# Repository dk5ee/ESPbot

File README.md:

# ESPbot
Another ESP32-cam based robot project

The repository contains:

* espcam - kicad footprint and library for ESP32-CAM
* TP5400 - kicad footprint and library for TP5400 and ESOP-8
* espbot - kicad project for a motherboard, clone of https://github.com/c3d2/C3-PR/tree/master/pcb

## Considerations TBD

* 0402 or 0805 or other footprints for resistors - make the pcb easier or make it smaller
* same for capacitors
* also capacitors: MLCC or electrolytics for the microfarad caps
* document the reset logic - does this work as intended?
* footprint for the inductor
* which usb socket?
* maximum pcb dimensions - more squarish or more longish?
* also pcb: where should the camera be located on the the assembly - more in the middle or on a side?
* also pcb: where should the antenna be located? on top, protruding over the edge of the motherboard?
* heat problem: the tp5400 and the esp32 will generate heat
* maybe power the motordriver directly from battery power, if the motor allows that
* consider alternatives to TP4500
* the inverters to save pins eliminate the possibility to do a motor brake

## Differences to C3-PR design

* made with kicad instead of easyeda
* instead of power from a USB powerbank this design uses a TP4500 power management chip
* instead of the dual NPN transistor every transistor is the same mosfet

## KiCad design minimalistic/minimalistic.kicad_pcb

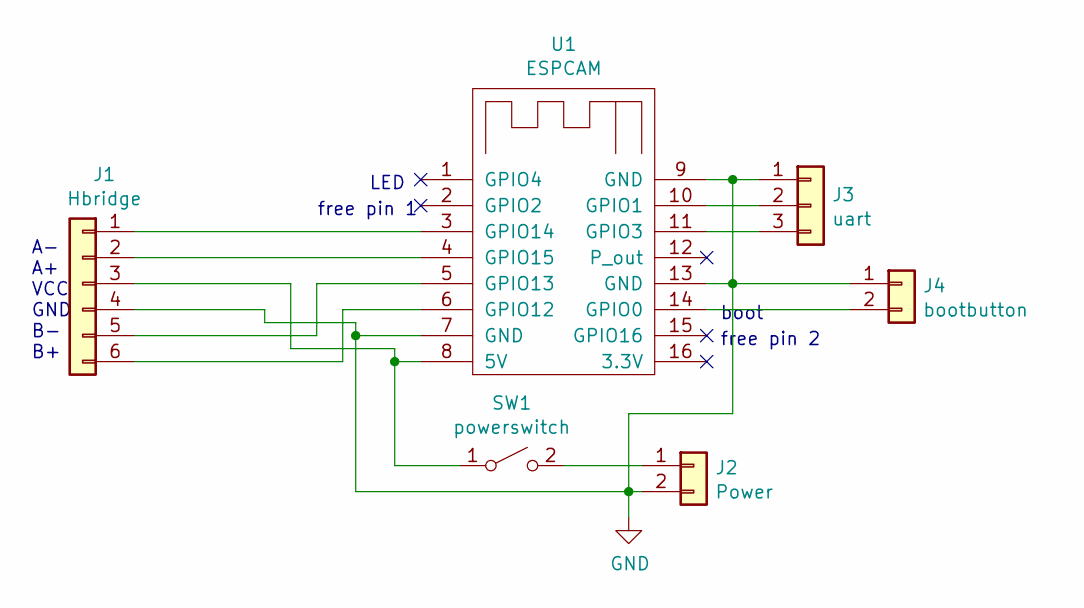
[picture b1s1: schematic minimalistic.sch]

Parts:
J1: Hbridge; PinHeader_1x06_P2.54mm_Vertical
J2: Power; JST_EH_B2B-EH-A_1x02_P2.50mm_Vertical
J3: uart; PinHeader_1x03_P2.54mm_Vertical
J4: bootbutton; PinHeader_1x02_P2.54mm_Vertical
SW1: powerswitch; PinHeader_1x02_P2.54mm_Vertical
U1: ESPCAM; ESPCAM_bottom

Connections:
GND: J1.4, J2.2, J3.1, J4.1, U1.7 (GND), U1.9 (GND), U1.13 (GND)
unnamed: J1.1, U1.3 (GPIO14)
unnamed: J1.2, U1.4 (GPIO15)
unnamed: J1.3, SW1.1 (A), U1.8 (5V)
unnamed: J1.5, U1.5 (GPIO13)
unnamed: J1.6, U1.6 (GPIO12)
unnamed: J2.1, SW1.2 (B)
unnamed: J3.2, U1.10 (GPIO1)
unnamed: J3.3, U1.11 (GPIO3)
unnamed: J4.2, U1.14 (GPIO0)

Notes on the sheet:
A- A+ VCC GND B- B+
LED
boot
free pin 1
free pin 2

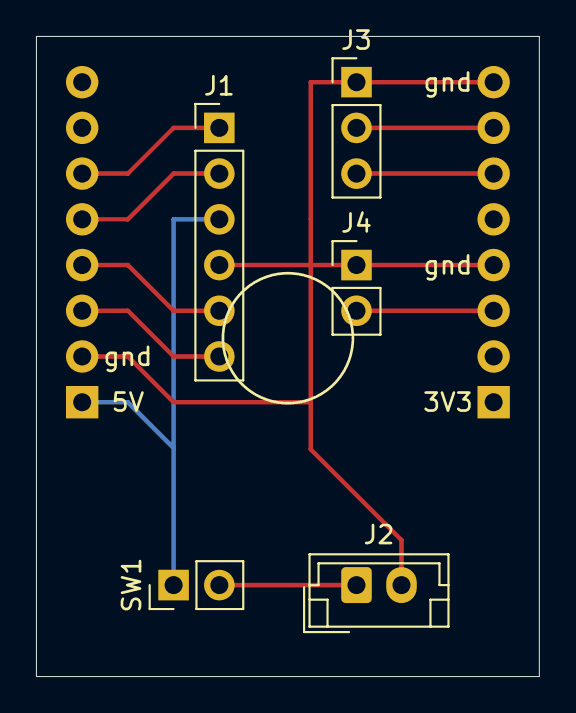
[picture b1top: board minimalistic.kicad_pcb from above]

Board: 2 copper layers, 27.9 x 35.6 mm, 6 parts (0 on the bottom side), 10 nets.

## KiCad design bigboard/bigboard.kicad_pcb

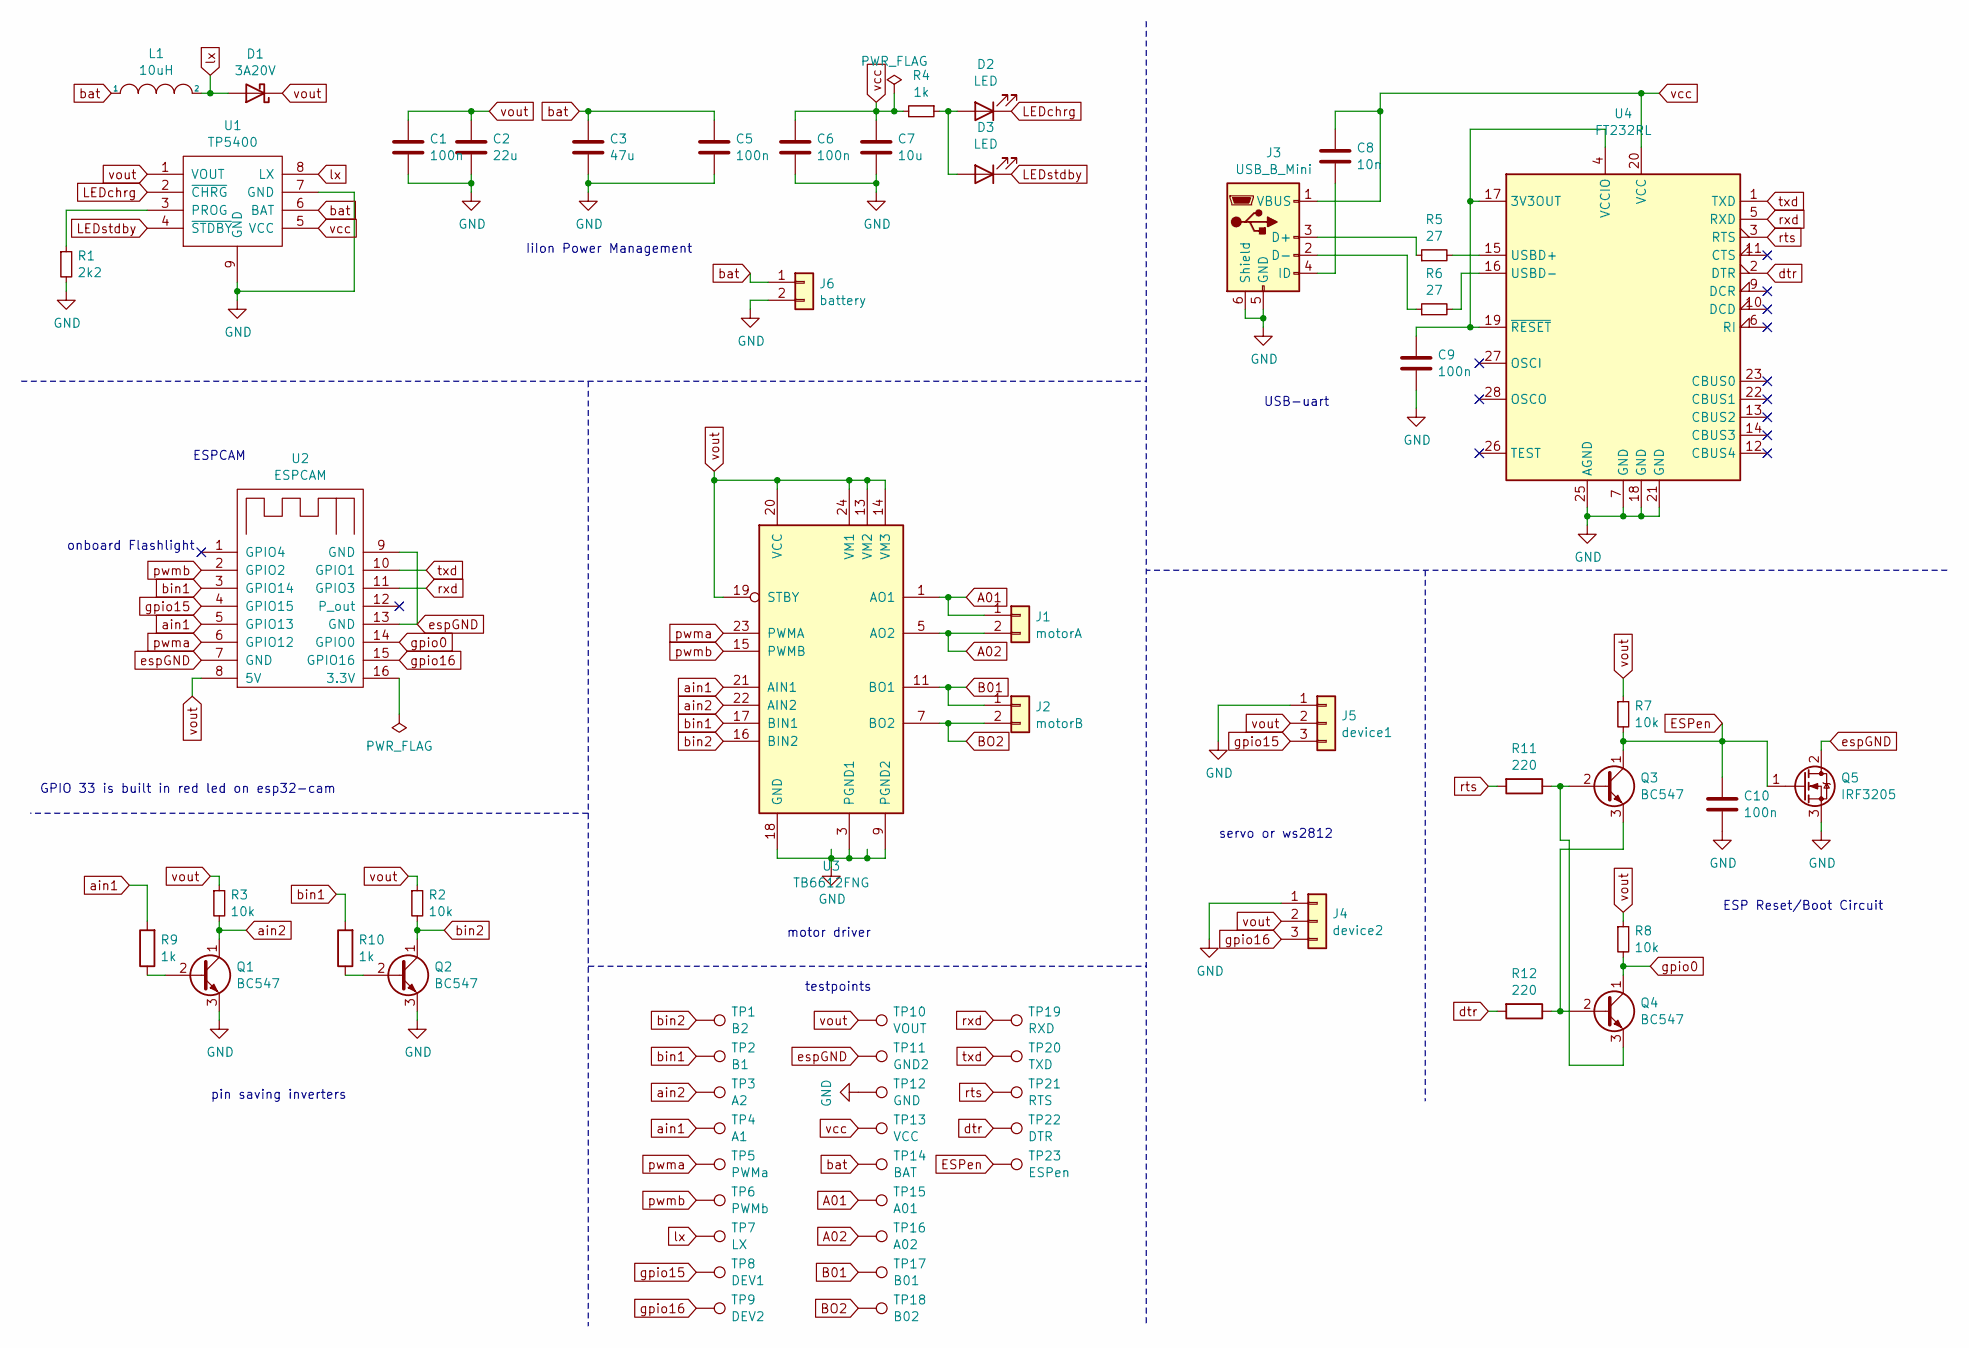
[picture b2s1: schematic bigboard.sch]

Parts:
C1, C5, C6, C9, C10: 100n; C_Disc_D3.0mm_W1.6mm_P2.50mm
C2: 22u; CP_Radial_D10.0mm_P2.50mm_P5.00mm
C3: 47u; CP_Radial_D10.0mm_P2.50mm_P5.00mm
C7: 10u; CP_Radial_D10.0mm_P2.50mm_P5.00mm
C8: 10n; C_Disc_D4.3mm_W1.9mm_P5.00mm
D1: 3A20V; D_A-405_P7.62mm_Horizontal
D2, D3: LED; LED_D3.0mm
J1: motorA; PinHeader_1x02_P2.54mm_Vertical
J2: motorB; PinHeader_1x02_P2.54mm_Vertical
J3: USB_B_Mini; USB_Micro-B_Amphenol_10118194_Horizontal
J4: device2; PinHeader_1x03_P2.54mm_Vertical
J5: device1; PinHeader_1x03_P2.54mm_Vertical
J6: battery; PinHeader_1x02_P2.54mm_Vertical
L1: 10uH; L_Toroid_Vertical_L10.0mm_W5.0mm_P5.08mm
Q1, Q2, Q3, Q4: BC547; TO-92_Inline
Q5: IRF3205; TO-220F-3_Horizontal_TabDown
R1: 2k2; R_Axial_DIN0204_L3.6mm_D1.6mm_P5.08mm_Horizontal
R2, R3, R7, R8: 10k; R_Axial_DIN0204_L3.6mm_D1.6mm_P5.08mm_Horizontal
R4, R9, R10: 1k; R_Axial_DIN0204_L3.6mm_D1.6mm_P5.08mm_Horizontal
R5, R6: 27; R_Axial_DIN0204_L3.6mm_D1.6mm_P5.08mm_Horizontal
R11, R12: 220; R_Axial_DIN0204_L3.6mm_D1.6mm_P5.08mm_Horizontal
TP1: B2; TestPoint_Bridge_Pitch2.54mm_Drill0.7mm
TP2: B1; TestPoint_Bridge_Pitch2.54mm_Drill0.7mm
TP3: A2; TestPoint_Bridge_Pitch2.54mm_Drill0.7mm
TP4: A1; TestPoint_Bridge_Pitch2.54mm_Drill0.7mm
TP5: PWMa; TestPoint_Bridge_Pitch2.54mm_Drill0.7mm
TP6: PWMb; TestPoint_Bridge_Pitch2.54mm_Drill0.7mm
TP7: LX; TestPoint_Bridge_Pitch2.54mm_Drill0.7mm
TP8: DEV1; TestPoint_Bridge_Pitch2.54mm_Drill0.7mm
TP9: DEV2; TestPoint_Bridge_Pitch2.54mm_Drill0.7mm
TP10: VOUT; TestPoint_Bridge_Pitch2.54mm_Drill0.7mm
TP11: GND2; TestPoint_Bridge_Pitch2.54mm_Drill0.7mm
TP12: GND; TestPoint_Bridge_Pitch2.54mm_Drill0.7mm
TP13: VCC; TestPoint_Bridge_Pitch2.54mm_Drill0.7mm
TP14: BAT; TestPoint_Bridge_Pitch2.54mm_Drill0.7mm
TP15: A01; TestPoint_Bridge_Pitch2.54mm_Drill0.7mm
TP16: A02; TestPoint_Bridge_Pitch2.54mm_Drill0.7mm
TP17: B01; TestPoint_Bridge_Pitch2.54mm_Drill0.7mm
TP18: B02; TestPoint_Bridge_Pitch2.54mm_Drill0.7mm
TP19: RXD; TestPoint_Bridge_Pitch2.54mm_Drill0.7mm
TP20: TXD; TestPoint_Bridge_Pitch2.54mm_Drill0.7mm
TP21: RTS; TestPoint_Bridge_Pitch2.54mm_Drill0.7mm
TP22: DTR; TestPoint_Bridge_Pitch2.54mm_Drill0.7mm
TP23: ESPen; TestPoint_Bridge_Pitch2.54mm_Drill0.7mm
U1: TP5400; ESOP8-F.Cu-only
U2: ESPCAM; ESPCAM_bottom
U3: TB6612FNG; SSOP-24_5.3x8.2mm_P0.65mm
U4: FT232RL; SSOP-28_5.3x10.2mm_P0.65mm

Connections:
A01: J1.1, TP15.1, U3.1 (AO1), U3.2 (AO1)
A02: J1.2, TP16.1, U3.5 (AO2), U3.6 (AO2)
B01: J2.1, TP17.1, U3.11 (BO1), U3.12 (BO1)
BO2: J2.2, TP18.1, U3.7 (BO2), U3.8 (BO2)
ESPen: C10.1, Q3.1 (C), Q5.1 (G), R7.2, TP23.1
GND: C1.2, C2.2, C3.2, C5.2, C6.2, C7.2, C9.2, C10.2, J3.5 (GND), J3.6 (Shield), J4.1, J5.1, J6.2, Q1.3 (E), Q2.3 (E), Q5.3 (S), R1.2, TP12.1, U1.7 (GND), U1.9 (GND), U3.3 (PGND1), U3.4 (PGND1), U3.9 (PGND2), U3.10 (PGND2), U3.18 (GND), U4.7 (GND), U4.18 (GND), U4.21 (GND), U4.25 (AGND)
LEDchrg: D2.1 (K), U1.2 (~CHRG)
LEDstdby: D3.1 (K), U1.4 (~STDBY)
unnamed: C8.2, J3.4 (ID)
unnamed: C9.1, U4.4 (VCCIO), U4.17 (3V3OUT), U4.19 (~RESET~)
unnamed: D2.2 (A), D3.2 (A), R4.1
unnamed: J3.2 (D-), R6.1
unnamed: J3.3 (D+), R5.1
unnamed: Q1.2 (B), R9.1
unnamed: Q2.2 (B), R10.1
unnamed: Q3.2 (B), Q4.3 (E), R11.1
unnamed: Q3.3 (E), Q4.2 (B), R12.1
unnamed: R1.1, U1.3 (PROG)
unnamed: R5.2, U4.15 (USBD+)
unnamed: R6.2, U4.16 (USBD-)
ain1: R9.2, TP4.1, U2.5 (GPIO13), U3.21 (AIN1)
ain2: Q1.1 (C), R3.2, TP3.1, U3.22 (AIN2)
bat: C3.1, C5.1, J6.1, L1.1, TP14.1, U1.6 (BAT)
bin1: R10.2, TP2.1, U2.3 (GPIO14), U3.17 (BIN1)
bin2: Q2.1 (C), R2.2, TP1.1, U3.16 (BIN2)
dtr: R12.2, TP22.1, U4.2 (DTR)
espGND: Q5.2 (D), TP11.1, U2.7 (GND), U2.9 (GND), U2.13 (GND)
gpio0: Q4.1 (C), R8.2, U2.14 (GPIO0)
gpio15: J5.3, TP8.1, U2.4 (GPIO15)
gpio16: J4.3, TP9.1, U2.15 (GPIO16)
lx: D1.2 (A), L1.2, TP7.1, U1.8 (LX)
pwma: TP5.1, U2.6 (GPIO12), U3.23 (PWMA)
pwmb: TP6.1, U2.2 (GPIO2), U3.15 (PWMB)
rts: R11.2, TP21.1, U4.3 (RTS)
rxd: TP19.1, U2.11 (GPIO3), U4.5 (RXD)
txd: TP20.1, U2.10 (GPIO1), U4.1 (TXD)
vcc: C6.1, C7.1, C8.1, J3.1 (VBUS), R4.2, TP13.1, U1.5 (VCC), U4.20 (VCC)
vout: C1.1, C2.1, D1.1 (K), J4.2, J5.2, R2.1, R3.1, R7.1, R8.1, TP10.1, U1.1 (VOUT), U2.8 (5V), U3.13 (VM2), U3.14 (VM3), U3.19 (STBY), U3.20 (VCC), U3.24 (VM1)

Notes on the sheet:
IiIon Power Management
USB-uart
motor driver
ESPCAM
ESP Reset/Boot Circuit
onboard Flashlight
servo or ws2812
pin saving inverters
GPIO 33 is built in red led on esp32-cam
testpoints

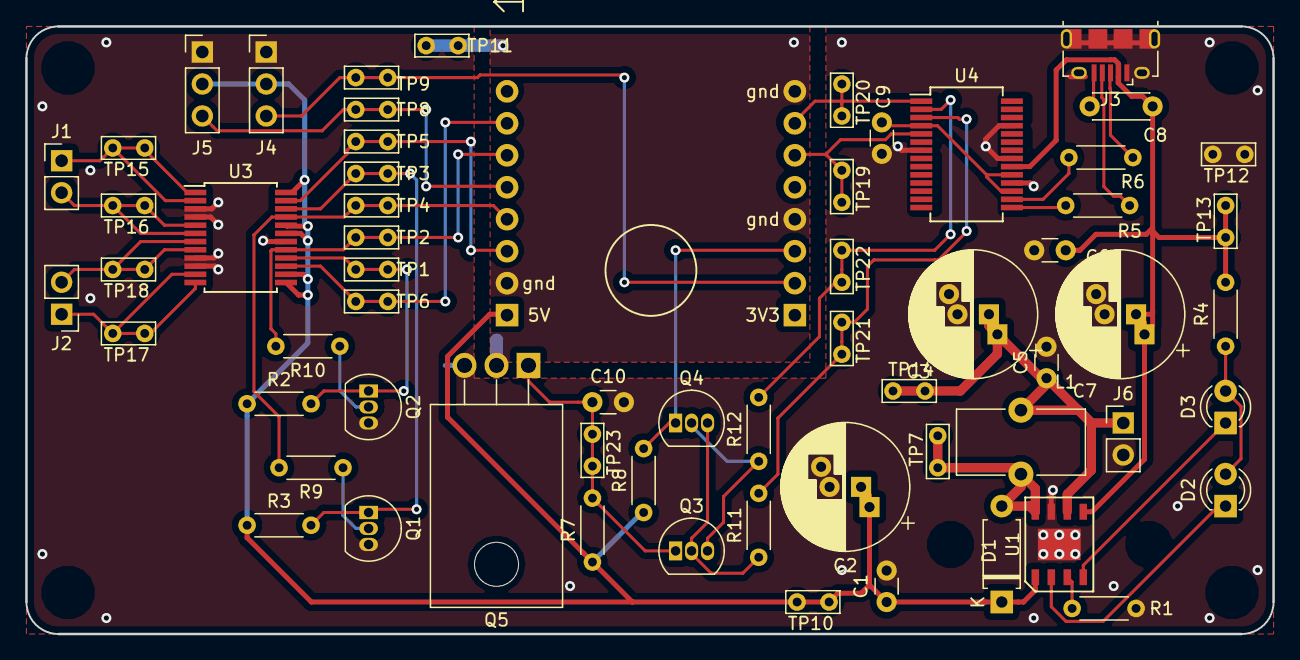
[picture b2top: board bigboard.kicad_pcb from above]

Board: 2 copper layers, 99.1 x 48.3 mm, 63 parts (0 on the bottom side), 38 nets.

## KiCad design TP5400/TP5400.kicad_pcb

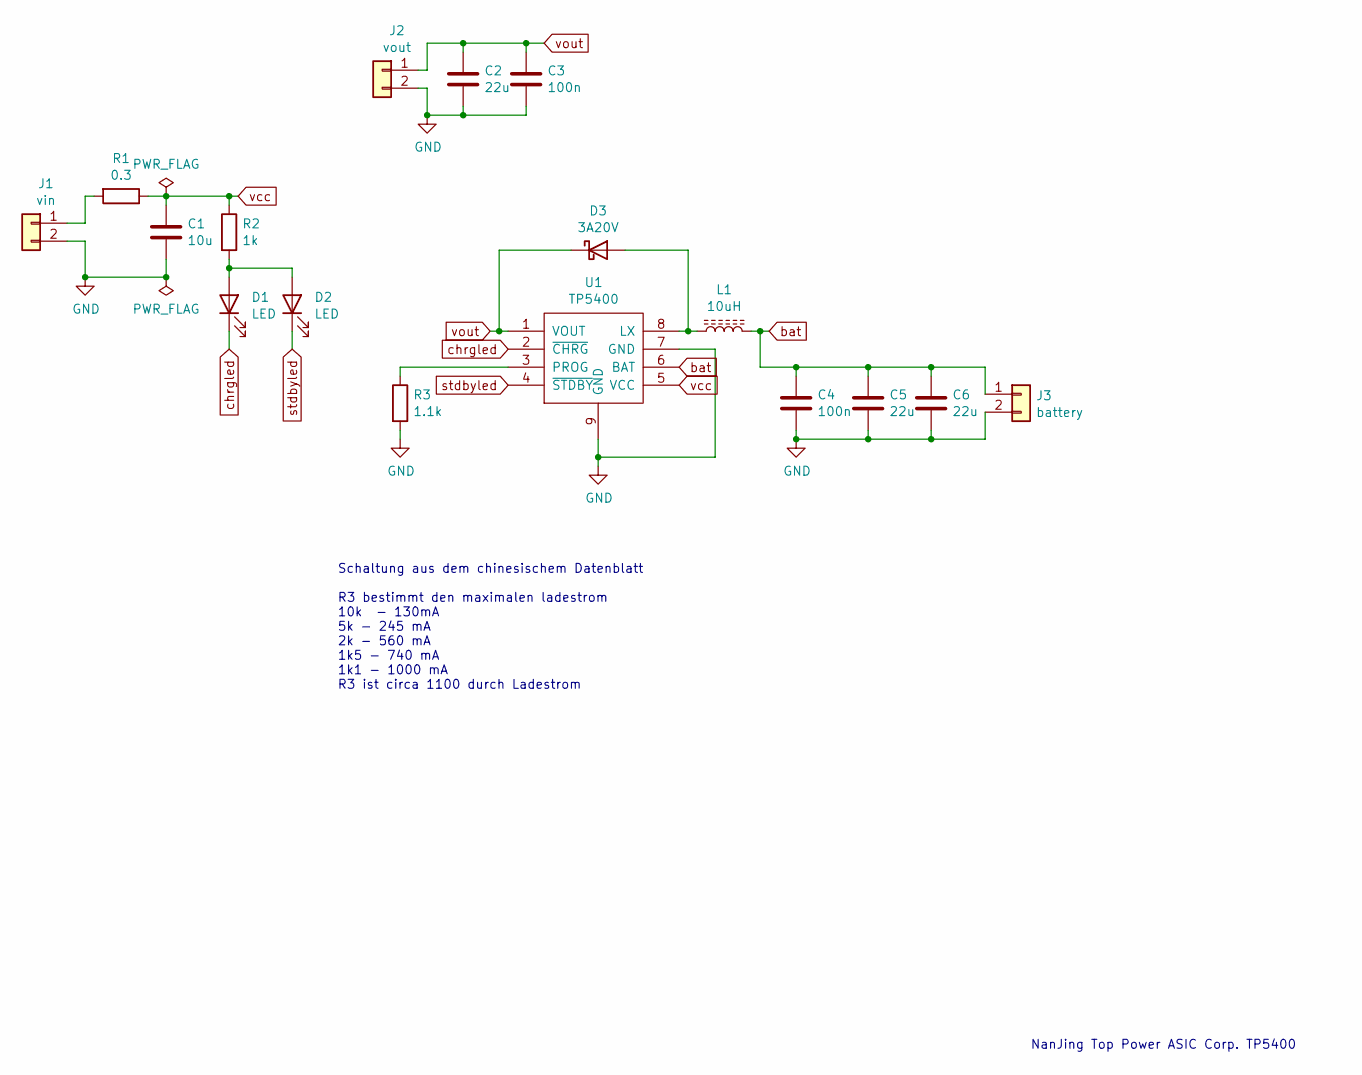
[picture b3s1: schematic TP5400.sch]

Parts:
C1: 10u; C_0805_2012Metric_Pad1.15x1.40mm_HandSolder
C2, C5, C6: 22u; C_0805_2012Metric_Pad1.15x1.40mm_HandSolder
C3, C4: 100n; C_0805_2012Metric_Pad1.15x1.40mm_HandSolder
D1, D2: LED; LED_0805_2012Metric_Pad1.15x1.40mm_HandSolder
D3: 3A20V; D_0805_2012Metric_Pad1.15x1.40mm_HandSolder
J1: vin; PinSocket_1x02_P2.54mm_Vertical
J2: vout; PinSocket_1x02_P2.54mm_Vertical
J3: battery; PinSocket_1x02_P2.54mm_Vertical
L1: 10uH; L_Wuerth_WE-PD-Typ-M-Typ-S_Handsoldering
R1: 0.3; R_0805_2012Metric_Pad1.15x1.40mm_HandSolder
R2: 1k; R_0805_2012Metric_Pad1.15x1.40mm_HandSolder
R3: 1.1k; R_0805_2012Metric_Pad1.15x1.40mm_HandSolder
U1: TP5400; ESOP8-F.Cu-only

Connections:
GND: C1.2, C2.2, C3.2, C4.2, C5.2, C6.2, J1.2, J2.2, J3.2, R3.2, U1.7 (GND), U1.9 (GND)
unnamed: D1.2 (A), D2.2 (A), R2.2
unnamed: D3.2 (A), L1.1, U1.8 (LX)
unnamed: J1.1, R1.2
unnamed: R3.1, U1.3 (PROG)
bat: C4.1, C5.1, C6.1, J3.1, L1.2, U1.6 (BAT)
chrgled: D1.1 (K), U1.2 (~CHRG)
stdbyled: D2.1 (K), U1.4 (~STDBY)
vcc: C1.1, R1.1, R2.1, U1.5 (VCC)
vout: C2.1, C3.1, D3.1 (K), J2.1, U1.1 (VOUT)

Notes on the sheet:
Schaltung aus dem chinesischem Datenblatt R3 bestimmt den maximalen ladestrom 10k - 130mA 5k - 245 mA 2k - 560 mA 1k5 - 740 mA 1k1 - 1000 mA R3 ist circa 1100 durch Ladestrom
NanJing Top Power ASIC Corp. TP5400

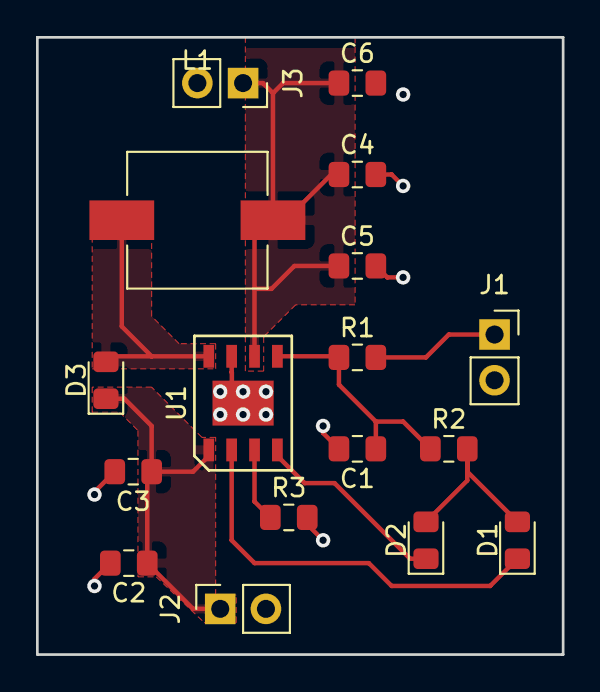
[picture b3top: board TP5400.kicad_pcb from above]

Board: 2 copper layers, 29.2 x 34.3 mm, 17 parts (0 on the bottom side), 10 nets.

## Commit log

2021-01-23 more notes
2021-01-24 Update README.md, add gitignore
    The .gitignore is from https://github.com/github/gitignore, which is licensed under CC0
2021-01-24 fix and design of big board
2021-01-25 fix gitignore
2021-01-25 Fix Footprints for kicad 5.1.8
    thanks to tobi for the tip how to install a newer
    kicad on debian: there is a newer version in
    debian-packports.
    fixed the libraries and footprints, and changed
    the path to relative ones.
2021-01-27 minimalistic pcb for prototyping
2021-01-29 working minimalistic board
